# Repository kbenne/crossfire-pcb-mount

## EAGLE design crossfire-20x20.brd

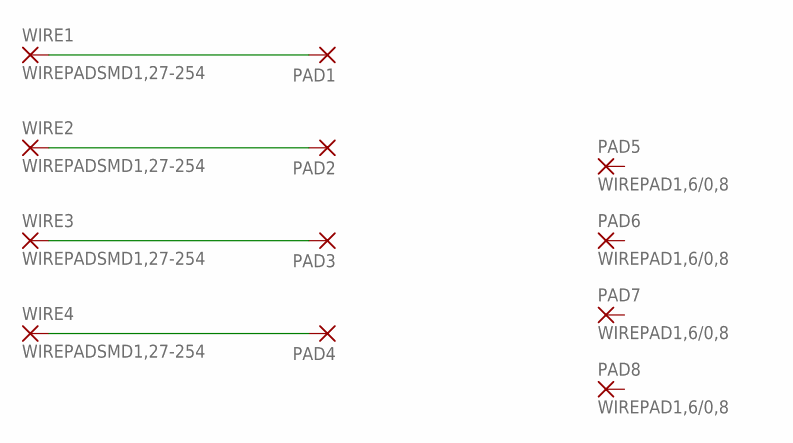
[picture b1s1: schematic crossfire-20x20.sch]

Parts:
PAD1, PAD2, PAD3, PAD4: 1,6/0,8
PAD5, PAD6, PAD7, PAD8: WIREPAD1,6/0,8; 1,6/0,8
WIRE1, WIRE2, WIRE3, WIRE4: WIREPADSMD1,27-254; SMD1,27-2,54

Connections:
unnamed: PAD1.1, WIRE1.1
unnamed: PAD2.1, WIRE2.1
unnamed: PAD3.1, WIRE3.1
unnamed: PAD4.1, WIRE4.1

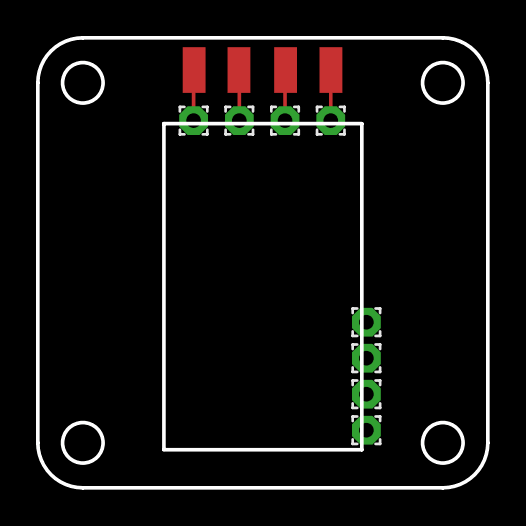
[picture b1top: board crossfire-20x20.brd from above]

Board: 2 copper layers, 25.0 x 25.0 mm, 12 parts (0 on the bottom side), 4 nets.

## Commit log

2021-02-03 Initial 20x20 and 30x30 board
